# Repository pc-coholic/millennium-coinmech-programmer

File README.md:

# millennium-coinmech-programmer
Programmer-Hardware for Coinmech found in Nortel/Quortech Millennium Payphones

## Hardware
The PCB fits a [dirtypcbs.com](http://dirtypcbs.com) 5x5 protopack-panel. You can order a copy of the board directly at dirtypcbs.com using [this link](http://dirtypcbs.com/store/designer/details/13026/1100/millennium-payphone-coinmech-programmer).

In fact, the PCB is just a carrier for a common red, chinese FTDI232R-board. You will also need to add a pinheader or barrel-connector (to get power from the payphone or inject 12V directly - not both though!).

A limited amount of fully assembled and tested PCBs are available for purchase by contacting me at `martin @ $github-username$  .de`

## Software
In the long run, the programmer will be used with the web-platform running at [http://millennium.management/](http://millennium.management/). In the meantime, feel free to use the python-scripts provided in the `tests`-folder.

### Requirements
* python3
* pylibftdi
* libftdi (sometimes called libftdi1)

It is recommended, that you install the provided `99-libftdi.rules`-files in the udev-rule-folder (eg. `/etc/udev/rules.d/`). That way, any attached FTDI-device is available to users in the `dialout`-group. If you choose to not install the udev-rule (or to install the rule but to not put your user in the `dialout`-group), the python-scripts will need `root` to run.

### Known issues
* The dumper-example just outputs the contents of the validator-EEPROM onto the console in hex-notation and does not write a file.
* There is no script yet to write the dump of a validator back into the device. It's not difficult to do this - but if you want to roll your own script in the meantime, please be advised, that it is not known yet, what all fields of the validator do. If in doubt, only overwrite the coin-definitions and nothing else. Also, please be aware, that changing the fist Byte of the EEPROM to anything else than `0x03` might brick your device.

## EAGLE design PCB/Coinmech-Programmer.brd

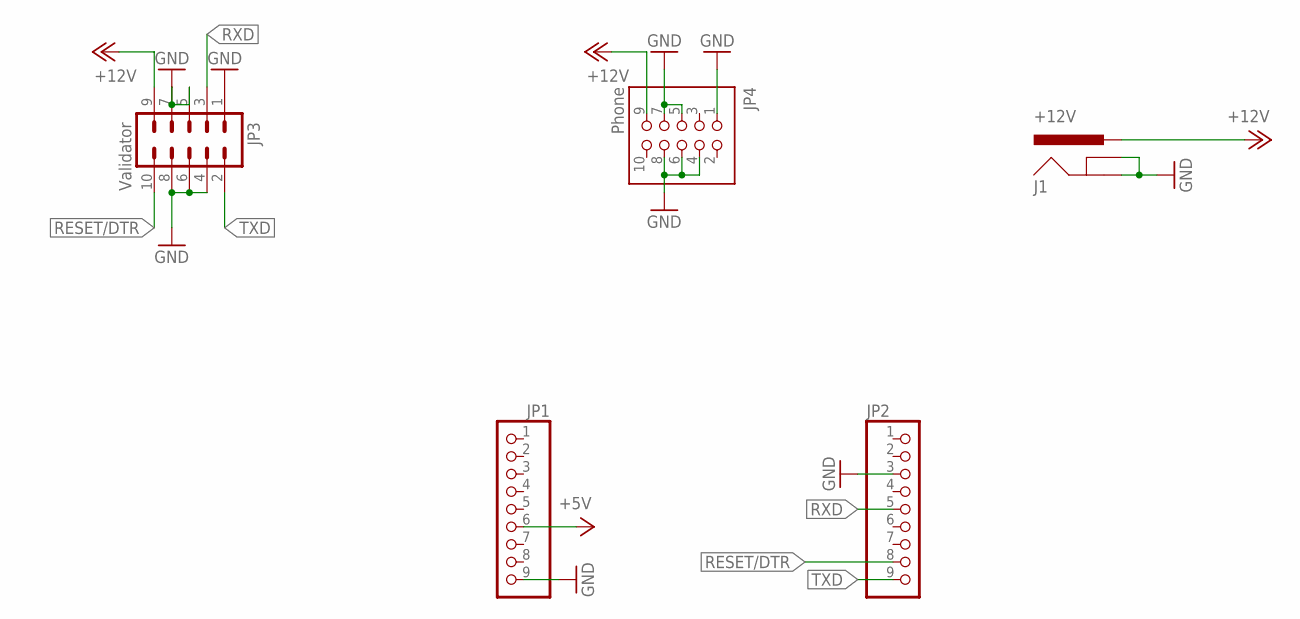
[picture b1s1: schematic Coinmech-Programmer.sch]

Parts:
J1: +12V; POWER_JACK_PTH
JP1, JP2: PINHD-1X9; 1X09
JP3: Validator; 2X5-SHROUDED
JP4: Phone; 2X05

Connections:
+5V: JP1.6
+12V: J1.PWR, JP3.9, JP4.9
GND: J1.GND, J1.GNDBREAK, JP1.9, JP2.3, JP3.1, JP3.4, JP3.5, JP3.6, JP3.7, JP3.8, JP4.1, JP4.4, JP4.5, JP4.6, JP4.7, JP4.8
RESET/DTR: JP2.8, JP3.10
RXD: JP2.5, JP3.3
TXD: JP2.9, JP3.2

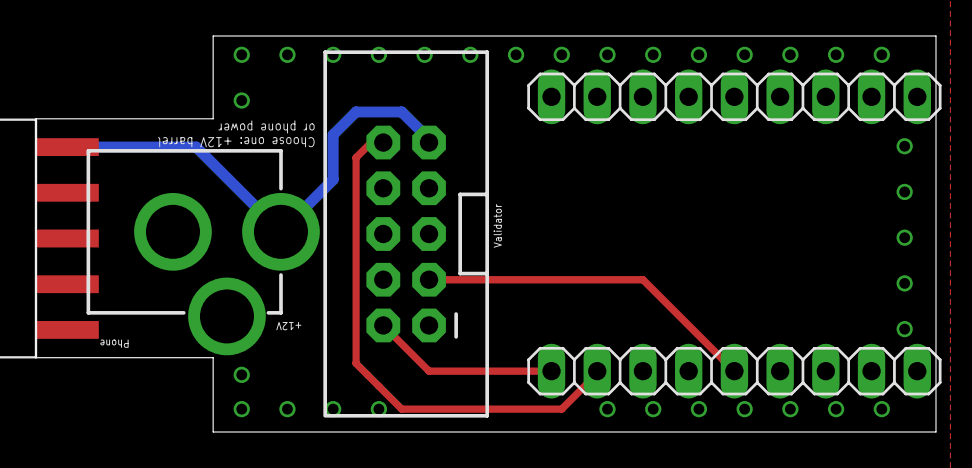
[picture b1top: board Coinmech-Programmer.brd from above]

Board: 2 copper layers, 50.0 x 22.0 mm, 5 parts (1 on the bottom side), 5 nets.

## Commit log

2016-12-10 Adding PCB-files
2016-12-10 Adding dumper

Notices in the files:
parts and their libraries:
SparkFun-Connectors: Licensing: Creative Commons ShareAlike 4.0 International - https://creativecommons.org/licenses/by-sa/4.0
